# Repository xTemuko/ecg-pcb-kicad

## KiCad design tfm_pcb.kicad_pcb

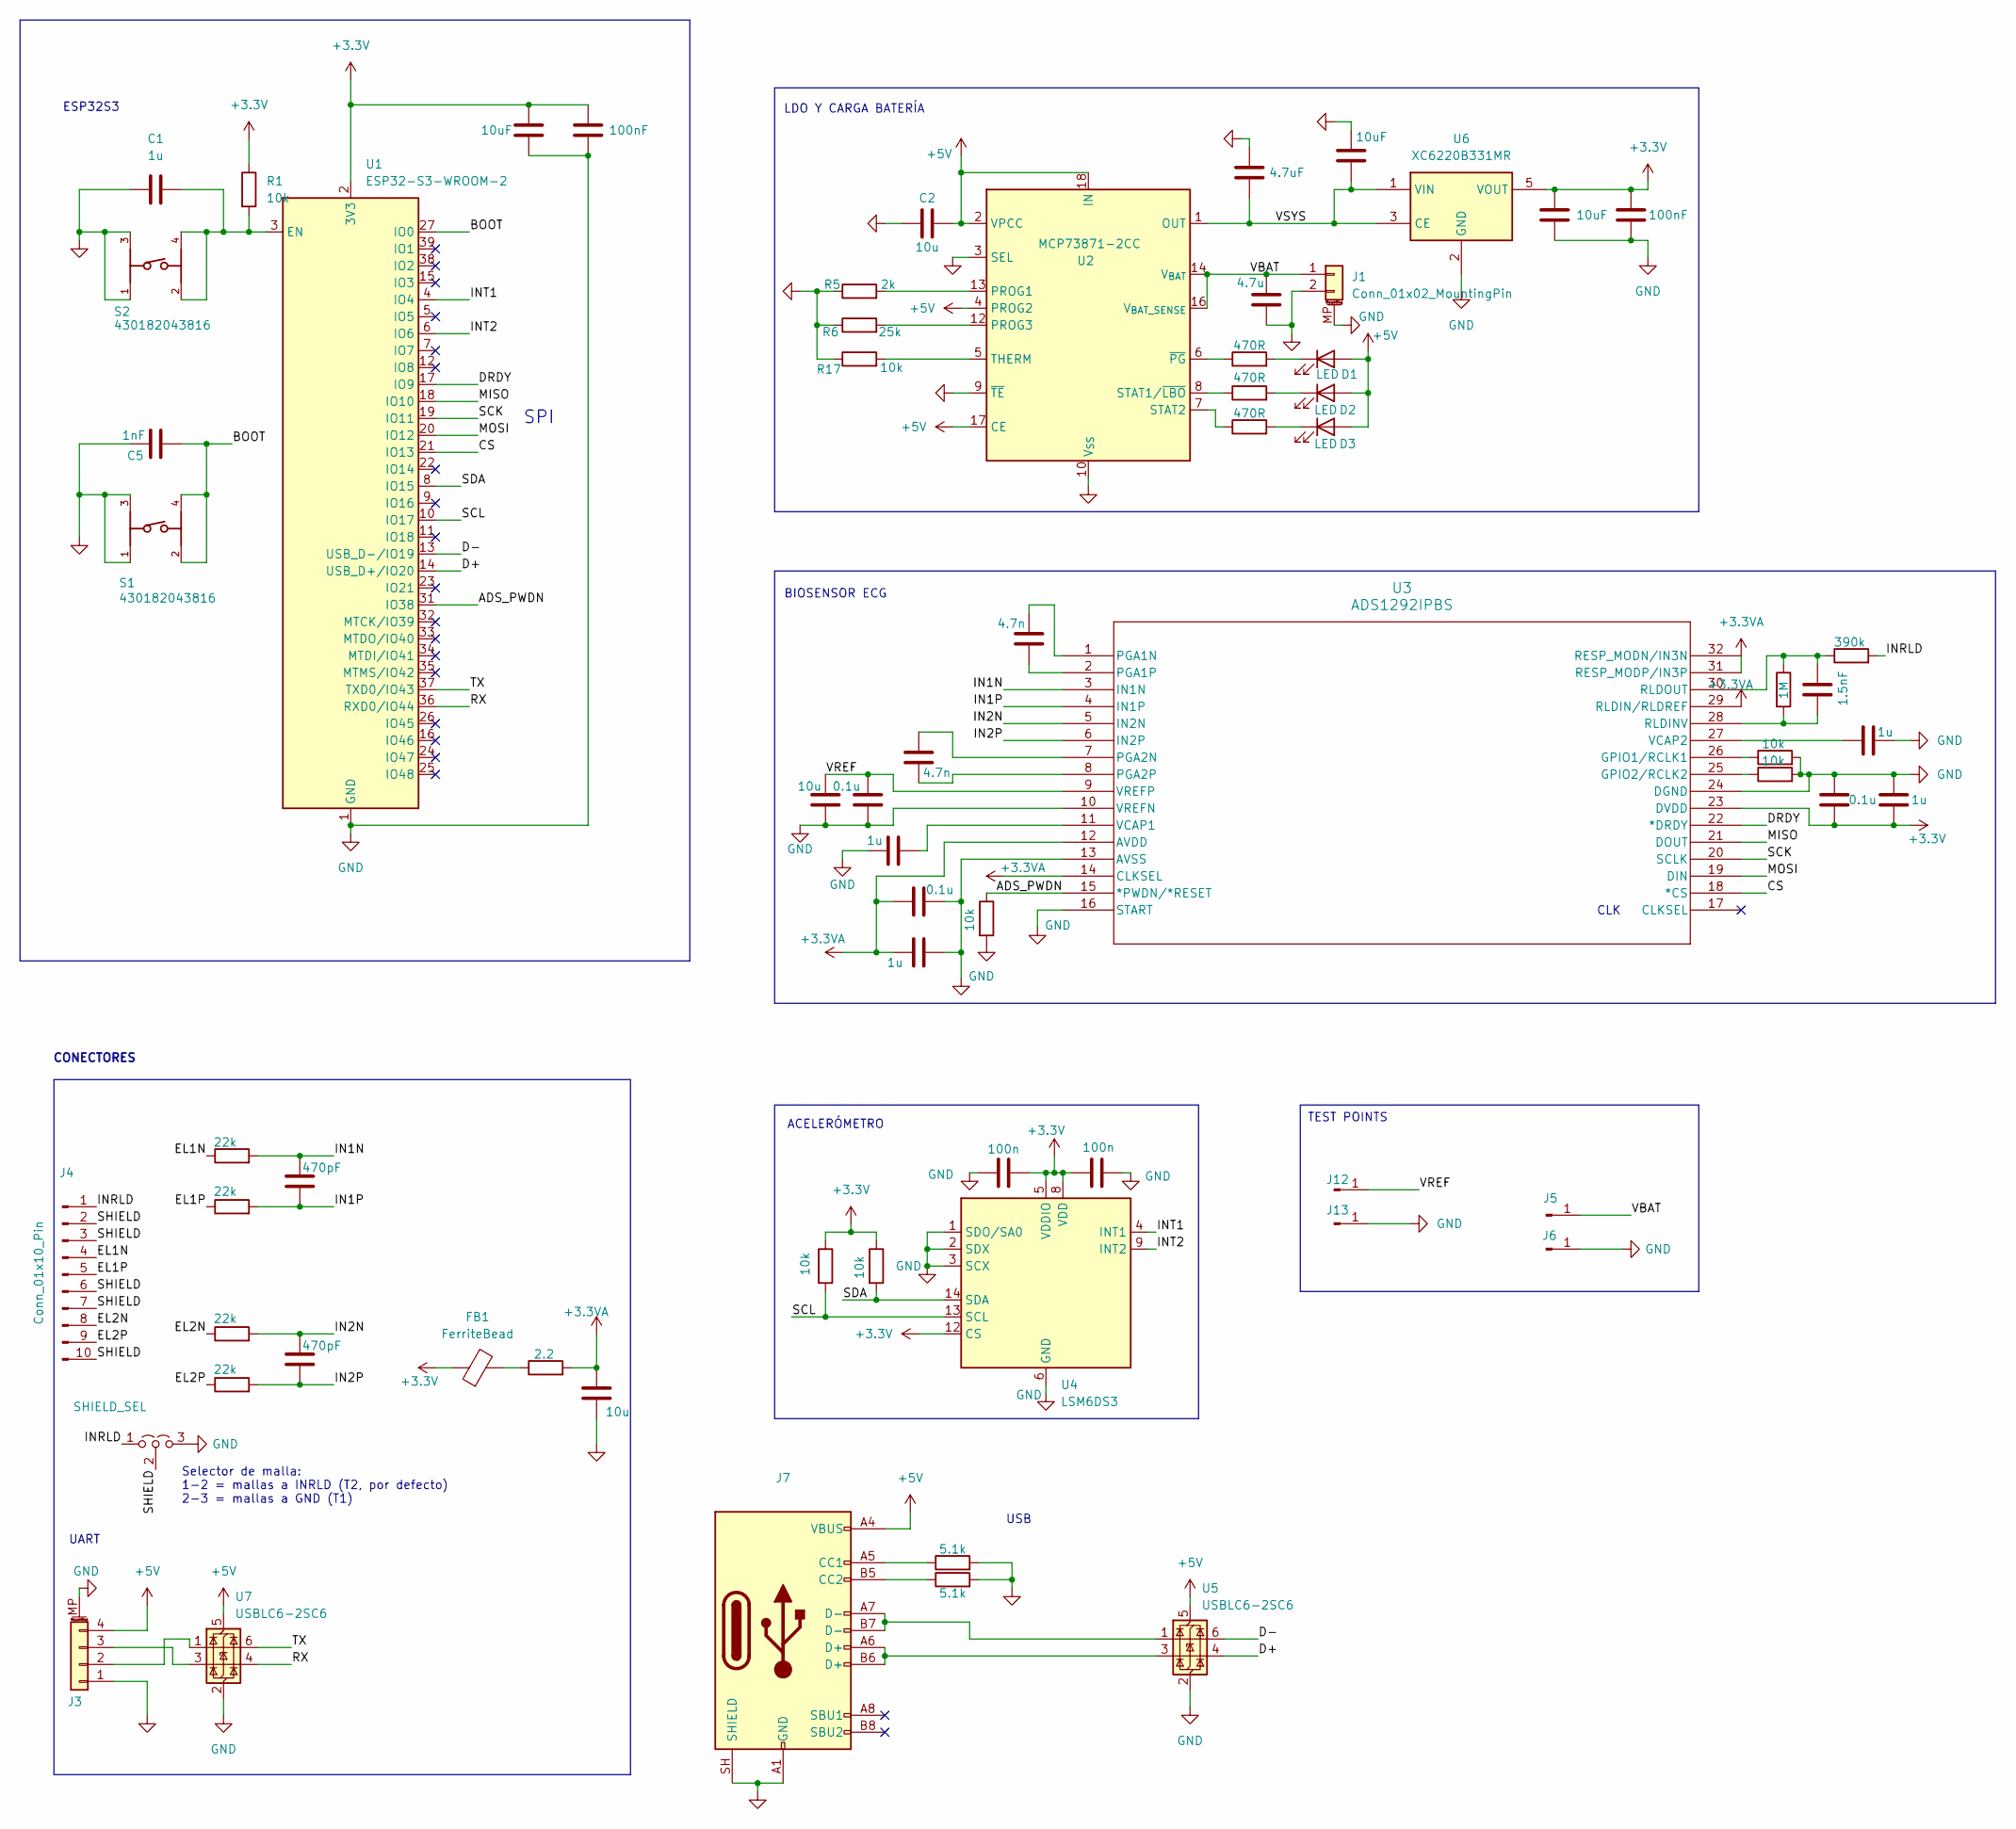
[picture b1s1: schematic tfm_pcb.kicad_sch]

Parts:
C1, C7, C9, C10: 1u; C_0603_1608Metric
C2: 10u; C_0805_2012Metric
C3: 4.7u; C_0805_2012Metric
C4: 4.7uF; C_0805_2012Metric
C5: 1nF; C_0603_1608Metric
C6: 0.1u; C_0603_1608Metric
C8, C13: 0.1u; C_0402_1005Metric
C11: 1u; C_0402_1005Metric
C12, C26: 10u; C_0603_1608Metric
C14, C15: 4.7n; C_0603_1608Metric
C16, C17: 470pF; C_0603_1608Metric
C18: 1.5nF; C_0603_1608Metric
C19, C20: 100n; C_0603_1608Metric
C21, C25: 100nF; C_0805_2012Metric
C22, C23, C24: 10uF; C_0805_2012Metric
D1, D2, D3: LED; LED_0805_2012Metric
FB1: FerriteBead; L_0603_1608Metric
J1: Conn_01x02_MountingPin; Molex_PicoBlade_53261-0271_1x02-1MP_P1.25mm_Horizontal
J3: Mounting Pin; Molex_PicoBlade_53261-0471_1x04-1MP_P1.25mm_Horizontal
J4: Conn_01x10_Pin; PinHeader_1x10_P2.54mm_Vertical
J5, J12: Conn_01x01_Pin; TestPoint_Pad_D1.0mm
J6, J13: Conn_01x01_Pin; TestPoint_Keystone_5000-5004_Miniature
J7: USB_C_Receptacle_USB2.0_16P; USB_C_Receptacle_HCTL_HC-TYPE-C-16P-01A
JP1: SHIELD_SEL; PinHeader_1x03_P2.54mm_Vertical
R1, R13, R14, R16, R17, R18, R19: 10k; R_0603_1608Metric
R2, R3, R4: 470R; R_0603_1608Metric
R5: 2k; R_0603_1608Metric
R6: 25k; R_0603_1608Metric
R7, R8, R9, R10: 22k; R_0603_1608Metric
R11: 1M; R_0603_1608Metric
R12: 390k; R_0603_1608Metric
R15: 2.2; R_0603_1608Metric
R20, R21: 5.1k; R_0603_1608Metric
S1, S2: 430182043816
U1: ESP32-S3-WROOM-2
U2: MCP73871-2CC; QFN-20-1EP_4x4mm_P0.5mm_EP2.5x2.5mm_ThermalVias
U3: ADS1292IPBS; PBS32
U4: LSM6DS3; LGA-14_3x2.5mm_P0.5mm_LayoutBorder3x4y
U5, U7: USBLC6-2SC6; SOT-23-6
U6: XC6220B331MR; SOT-23-5

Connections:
+3.3V: C6.2, C7.2, C19.1, C20.2, C21.2, C23.2, C24.2, C25.2, FB1.1, R1.1, R13.1, R14.1, U1.2 (3V3), U3.23 (DVDD), U4.5 (VDDIO), U4.8 (VDD), U4.12 (CS), U6.5 (VOUT)
+3.3VA: C8.1, C9.2, C26.1, R15.2, U3.12 (AVDD), U3.14 (CLKSEL), U3.29 (RLDIN/RLDREF), U3.31 (RESP_MODP/IN3P), U3.32 (RESP_MODN/IN3N)
+5V: C2.2, D1.2 (A), D2.2 (A), D3.2 (A), J3.4, J7.A4 (VBUS), J7.A9 (VBUS), J7.B4 (VBUS), J7.B9 (VBUS), U2.2 (VPCC), U2.4 (PROG2), U2.17 (CE), U2.18 (IN), U2.19 (IN), U5.5 (VBUS), U7.5 (VBUS)
/ADS_PWDN: R16.1, U1.31 (IO38), U3.15 (*PWDN/*RESET)
/BOOT: C5.2, S1.2, S1.4, U1.27 (IO0)
/CS: U1.21 (IO13), U3.18 (*CS)
/D+: U1.14 (USB_D+/IO20), U5.4 (I/O2)
/D-: U1.13 (USB_D-/IO19), U5.6 (I/O1)
/DRDY: U1.17 (IO9), U3.22 (*DRDY)
/EL1N: J4.4, R7.1
/EL1P: J4.5, R8.1
/EL2N: J4.8, R9.1
/EL2P: J4.9, R10.1
/IN1N: C16.1, R7.2, U3.3 (IN1N)
/IN1P: C16.2, R8.2, U3.4 (IN1P)
/IN2N: C17.1, R9.2, U3.5 (IN2N)
/IN2P: C17.2, R10.2, U3.6 (IN2P)
/INRLD: J4.1, JP1.1 (A), R12.2
/INT1: U1.4 (IO4), U4.4 (INT1)
/INT2: U1.6 (IO6), U4.9 (INT2)
/MISO: U1.18 (IO10), U3.21 (DOUT)
/MOSI: U1.20 (IO12), U3.19 (DIN)
/RX: U1.36 (RXD0/IO44), U7.4 (I/O2)
/SCK: U1.19 (IO11), U3.20 (SCLK)
/SCL: R13.2, U1.10 (IO17), U4.13 (SCL)
/SDA: R14.2, U1.8 (IO15), U4.14 (SDA)
/SHIELD: J4.2, J4.3, J4.6, J4.7, J4.10, JP1.2 (C)
/TX: U1.37 (TXD0/IO43), U7.6 (I/O1)
/VBAT: C3.2, J1.1, J5.1 (Pin_1_1), U2.14 (V_{BAT}), U2.15 (V_{BAT}), U2.16 (V_{BAT_SENSE})
/VREF: C12.2, C13.2, J12.1 (Pin_1_1), U3.9 (VREFP)
/VSYS: C4.1, C22.1, U2.1 (OUT), U2.20 (OUT), U6.1 (VIN), U6.3 (CE)
GND: C1.1, C2.1, C3.1, C4.2, C5.1, C6.1, C7.1, C8.2, C9.1, C10.2, C11.2, C12.1, C13.1, C19.2, C20.1, C21.1, C22.2, C23.1, C24.1, C25.1, C26.2, J1.2, J1.MP (MountPin), J3.1, J3.MP (MountPin), J6.1 (Pin_1_1), J7.A1 (GND), J7.A12 (GND), J7.B1 (GND), J7.B12 (GND), J7.SH (SHIELD), J13.1 (Pin_1_1), JP1.3 (B), R5.1, R6.1, R16.2, R17.1, R18.2, R19.2, R20.2, R21.2, S1.1, S1.3, S2.1, S2.3, U1.1 (GND), U1.40 (GND), U1.41 (GND), U2.3 (SEL), U2.9 (~TE), U2.10 (V_{SS}), U2.11 (V_{SS}), U2.21 (V_{SS}), U3.10 (VREFN), U3.13 (AVSS), U3.16 (START), U3.24 (DGND), U4.1 (SDO/SA0), U4.2 (SDX), U4.3 (SCX), U4.6 (GND), U4.7 (GND), U5.2 (GND), U6.2 (GND), U7.2 (GND)
unnamed: D1.1 (K), R3.2
unnamed: D2.1 (K), R4.2
unnamed: D3.1 (K), R2.2
unnamed: FB1.2, R15.1
unnamed: J3.2, U7.1 (I/O1)
unnamed: J3.3, U7.3 (I/O2)
unnamed: J7.A5 (CC1), R21.1
unnamed: J7.B5 (CC2), R20.1
unnamed: J7.A6 (D+), J7.B6 (D+), U5.3 (I/O2)
unnamed: J7.A7 (D-), J7.B7 (D-), U5.1 (I/O1)
unnamed: C1.2, R1.2, S2.2, S2.4, U1.3 (EN)
unnamed: R5.2, U2.13 (PROG1)
unnamed: R6.2, U2.12 (PROG3)
unnamed: R4.1, U2.8 (STAT1/~LBO)
unnamed: R2.1, U2.7 (STAT2)
unnamed: R17.2, U2.5 (THERM)
unnamed: R3.1, U2.6 (~PG)
unnamed: R19.1, U3.26 (GPIO1/RCLK1)
unnamed: R18.1, U3.25 (GPIO2/RCLK2)
unnamed: C15.1, U3.1 (PGA1N)
unnamed: C15.2, U3.2 (PGA1P)
unnamed: C14.1, U3.7 (PGA2N)
unnamed: C14.2, U3.8 (PGA2P)
unnamed: C18.2, R11.2, U3.28 (RLDINV)
unnamed: C18.1, R11.1, R12.1, U3.30 (RLDOUT)
unnamed: C11.1, U3.11 (VCAP1)
unnamed: C10.1, U3.27 (VCAP2)

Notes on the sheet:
USB
CLK
ACELERÓMETRO
BIOSENSOR ECG
ESP32S3
Selector de malla: 1-2 = mallas a INRLD (T2, por defecto) 2-3 = mallas a GND (T1)
UART
SPI
TEST POINTS
LDO Y CARGA BATERÍA
CONECTORES

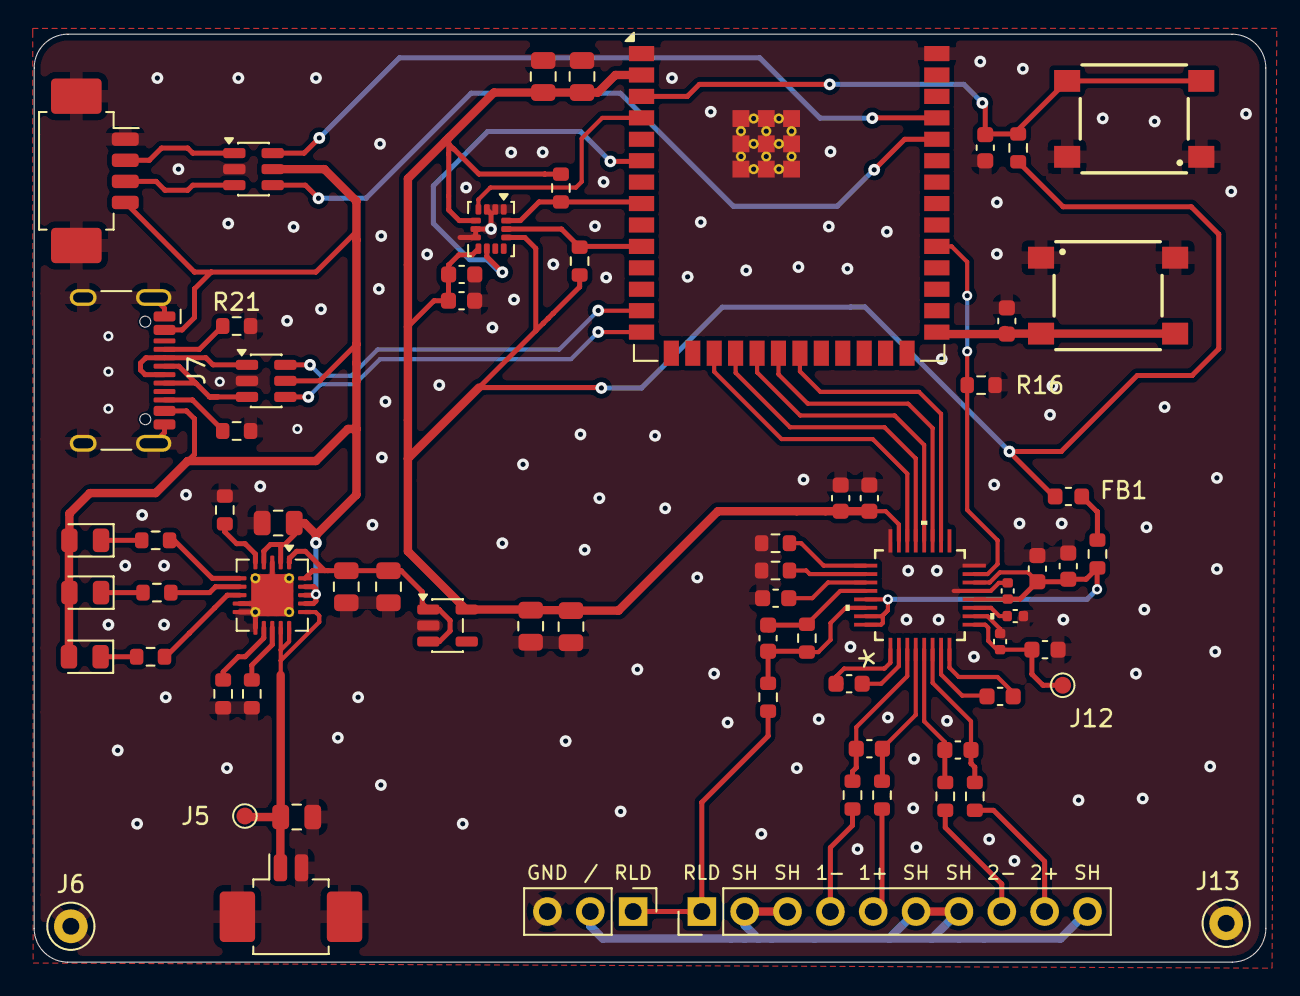
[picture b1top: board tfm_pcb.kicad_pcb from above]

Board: 2 copper layers, 73.0 x 55.0 mm, 69 parts (0 on the bottom side), 59 nets.
